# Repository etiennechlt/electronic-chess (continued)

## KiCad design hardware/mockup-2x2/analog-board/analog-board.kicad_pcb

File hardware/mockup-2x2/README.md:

# Maquette 2 x 2 : commande, montage, mise en route

> Remplacée par l'ADR 0010 : la maquette n'est plus construite, le
> plateau 8 x 8 est conçu directement en quadrants. Ce dossier reste
> la référence de la chaîne analogique et du routage. Depuis le
> 07/10/2026 sa carte bobines, rendue passive, est la carte du
> **pilote simple** et la carte analogique son shield possible :
> voir la [fiche du pilote](../../docs/bom-pilote.md).

Deux cartes (ADR 0008) : la carte bobines (100 x 100, 4 couches,
passive) et la carte analogique (100 x 62, 2 couches, assemblée). Le
MCU est une Nucleo-G474RE du commerce reliée en nappes Dupont.

## 0. Ouvrir les cartes dans KiCad

Chaque carte a son fichier projet `.kicad_pro` à côté du `.kicad_pcb`,
généré en même temps que lui : c'est ce fichier qu'on ouvre, KiCad ne
sachant pas ouvrir une carte seule depuis son gestionnaire de projet.

```bash
kicad hardware/mockup-2x2/analog-board/analog-board.kicad_pro
kicad hardware/mockup-2x2/coil-board/coil-board.kicad_pro
```

Sous macOS ou Windows, double clic sur le `.kicad_pro` (ou KiCad,
Fichier, Ouvrir un projet). La carte s'ouvre avec les règles du
générateur déjà en place : classe de nets, largeurs de piste et vias
proposés au routage, minima du DRC. Le projet de la carte analogique
associe aussi son schéma, ouvrable depuis le même gestionnaire.

Trois choses à savoir :

- Les fichiers sont au format KiCad 7. KiCad 8 ou 9 les ouvre et
  propose la conversion au premier enregistrement.
- Symboles et empreintes sont embarqués dans les fichiers : aucune
  bibliothèque à installer, aucune table de bibliothèques à régler.
- KiCad réécrit le `.kicad_pro` en enregistrant (état des fenêtres) et
  crée un `.kicad_prl` local, ignoré par git. Une régénération remet
  le projet dans son état canonique.

Sans KiCad : les rendus `docs/images/analog-board.png` et
`docs/images/coil-board.png`, ou les zip de gerbers dans une
visionneuse.

## 1. Commander

### Carte bobines (8 à 15 EUR les 5, plus l'option cuivre interne)

`sh hardware/mockup-2x2/coil-board/export.sh` regénère la carte et
produit `coil-board-gerbers.zip` (commité avec son empreinte). JLCPCB :
4 couches, 1,6 mm, 1 oz externe, cuivre interne 1 oz en option (note 23,
paragraphe 3.1), pas d'assemblage : la carte est passive, les LED sont
coupées par `leds.fitted` dans le yaml.

### Carte analogique (~60 EUR les 5 dont 2 assemblées)

`analog-board/` contient le projet KiCad, `jlc-bom.csv` et
`jlc-cpl.csv`. JLCPCB : 2 couches, 1,6 mm, assemblage face top.
Important : les codes LCSC du BOM sont des candidats plausibles saisis
hors ligne ; l'outil de commande JLC rapproche aussi par référence
fabricant (MPN) et signale tout écart : vérifier chaque ligne dans
leur prévisualisation avant de payer, en particulier TPS62150RGTR,
AD8421ARZ, OPA2810IDR, 74HCT4052PW, ADuM1201ARZ. Les composants
introuvables en assemblage (souvent l'AD8421) se commandent chez
Mouser ou DigiKey et se soudent à la main (SOIC, facile).

### Le reste (~70 EUR)

Voir `docs/bom-maquette.md` : Nucleo-G474RE, condensateurs C0G des
résonateurs, fil émaillé, aimants ferrite et N42, contreplaqué sec 3 à 6 mm,
feutre, visserie, impression des pièces de `mechanical/`.

## 2. Assembler

1. Carte analogique : souder les traversants (jack, barrettes J2 J4
   J5, JP1 JP3) ; laisser R66 et R67 non montées (elles court-circuitent
   l'isolateur UART).
2. Carte bobines : souder la barrette coudée 1 x 12 mâle pointant vers
   le nord ; entretoises M3 x 25 aux quatre coins.
3. Emboîter la barrette dans le connecteur femelle coudé J2 de la
   carte analogique : les deux cartes sont coplanaires, broche 1 sur
   broche 1 (x = 38,57 mm sur les deux).
4. Support d'aimant : visser la platine sous S3, monter la coupelle
   sur sa vis M3.
5. Bobiner les 4 résonateurs (gabarits imprimés, fil 0,25 mm, tours
   par classe donnés par `python -m chessboard_calc report`), souder
   chaque condensateur C0G, coller bobine et aimant dans les pucks,
   feutre dessous.
6. Percer la planche de contreplaqué avec le gabarit `surface-template`
   (trous de visserie et points lumineux des LED), puis la poser sur les
   entretoises au dessus de
   la carte bobines.

## 3. Câbler la Nucleo

Nappes Dupont femelle-femelle de J4 vers la Nucleo (UM2505), table
générée depuis `config/board.yaml` (section `nucleo_pins`) :

| J4 | Signal | Nucleo |
|---|---|---|
| 1 | 3V3 | 3V3 |
| 2, 4, 19 | GND | GND |
| 3 | AMP_OUT | A0 (PA0), en pont vers A1 (PA1) pour la voie B |
| 5 | MUX_A0 | D3 (PB3) |
| 6 | MUX_A1 | D4 (PB5) |
| 7 | MUX_INH | D5 (PB4) |
| 8 | PULSE_EN | A2 (PA4) |
| 9 a 12 | DRIVE1..4 | D11 (PA7), D12 (PA6), D14 (PB9), D15 (PB8) |
| 13 a 16 | DAMP1..4_N | D6 (PB10), D7 (PA8), D9 (PC7), D10 (PB6) |
| 17 | MCU_TX | D8 (PA9) |
| 18 | MCU_RX | D2 (PA10) |
| 20 | INA_OUT | libre (oscilloscope) |

## 4. Mise en route

1. Flasher `firmware/mockup` (`make`, copier le .bin sur le lecteur
   NUCLEO). Console VCP 921600 bauds.
2. Alimenter le 12 V (JP1 côté LDO pour commencer, JP3 côté FPWM).
3. `h` puis `s` : quatre lignes CSV. Sans puck, amp_mv doit rester
   faible ; poser un puck doit faire apparaître sa fréquence.
4. Vérifier la voie B au générateur de fonctions sur AMP_OUT (voir
   `firmware/mockup/README.md`, points à vérifier).
5. Dérouler `measurements/protocol.md`.

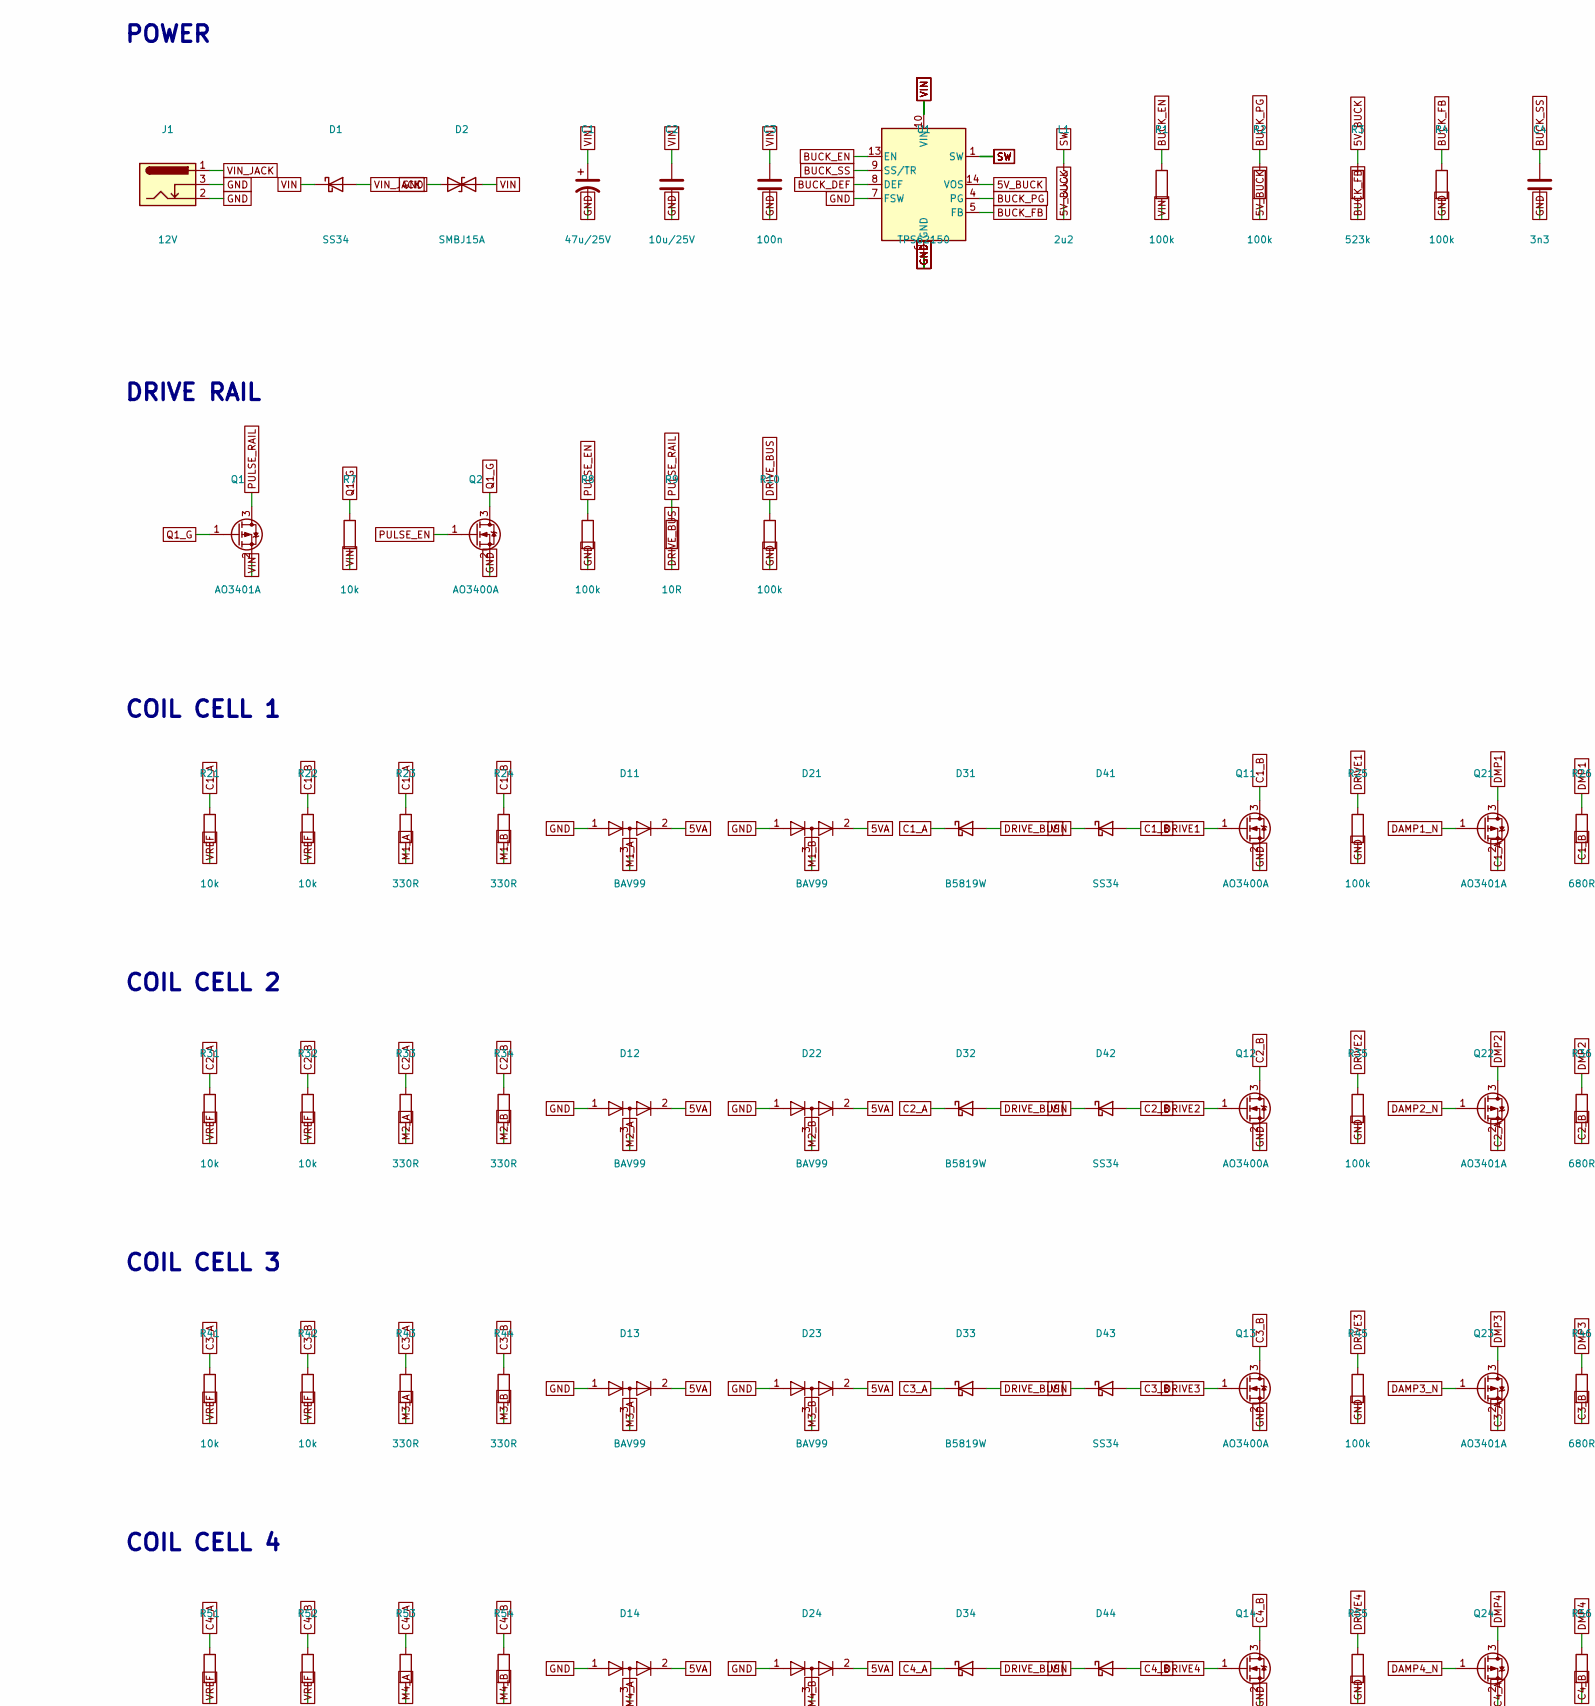
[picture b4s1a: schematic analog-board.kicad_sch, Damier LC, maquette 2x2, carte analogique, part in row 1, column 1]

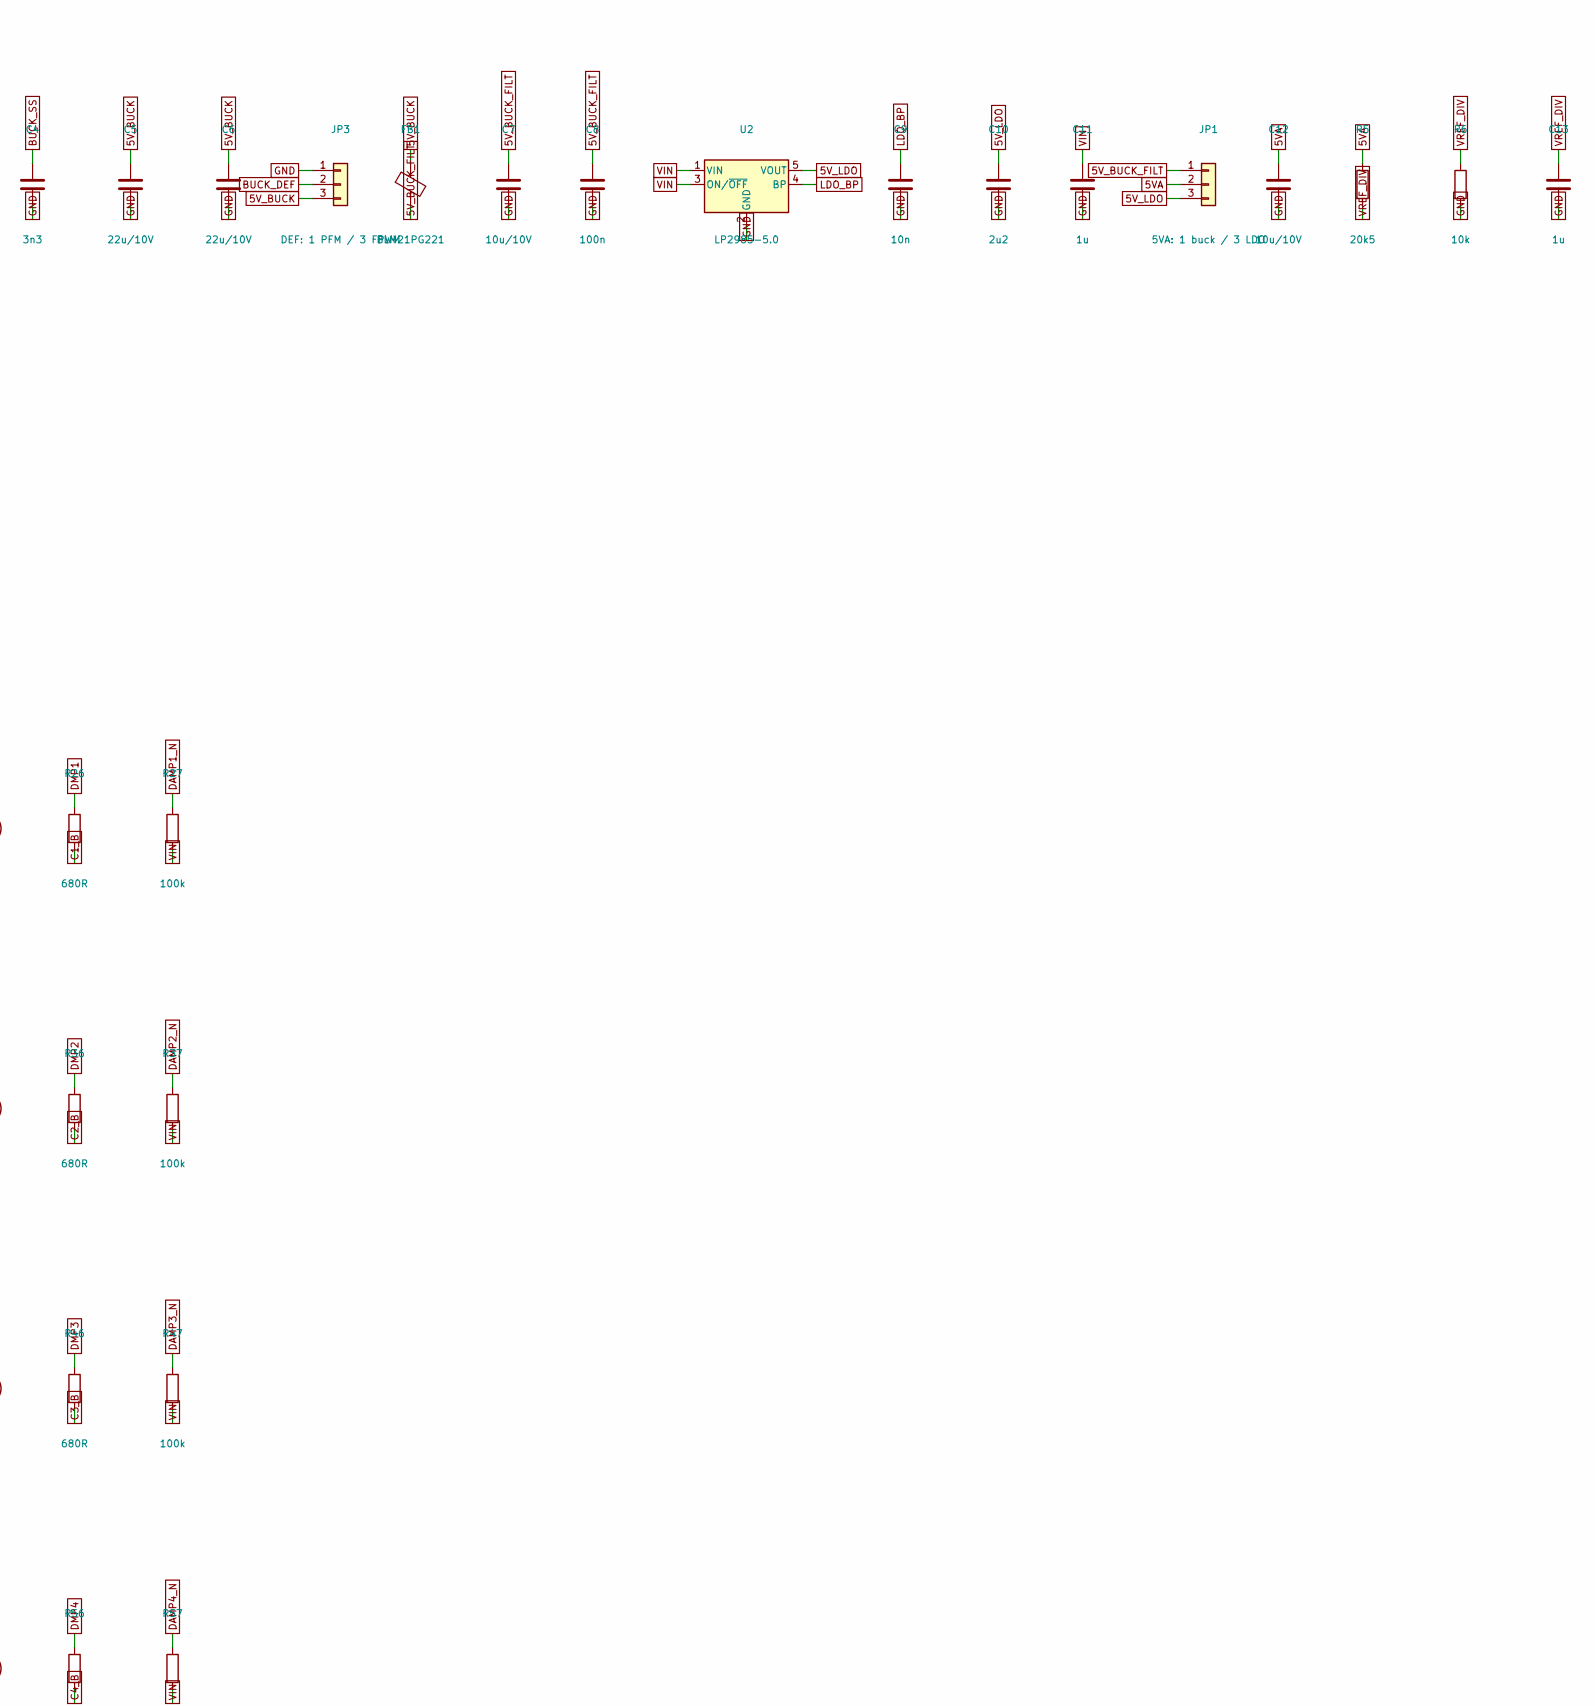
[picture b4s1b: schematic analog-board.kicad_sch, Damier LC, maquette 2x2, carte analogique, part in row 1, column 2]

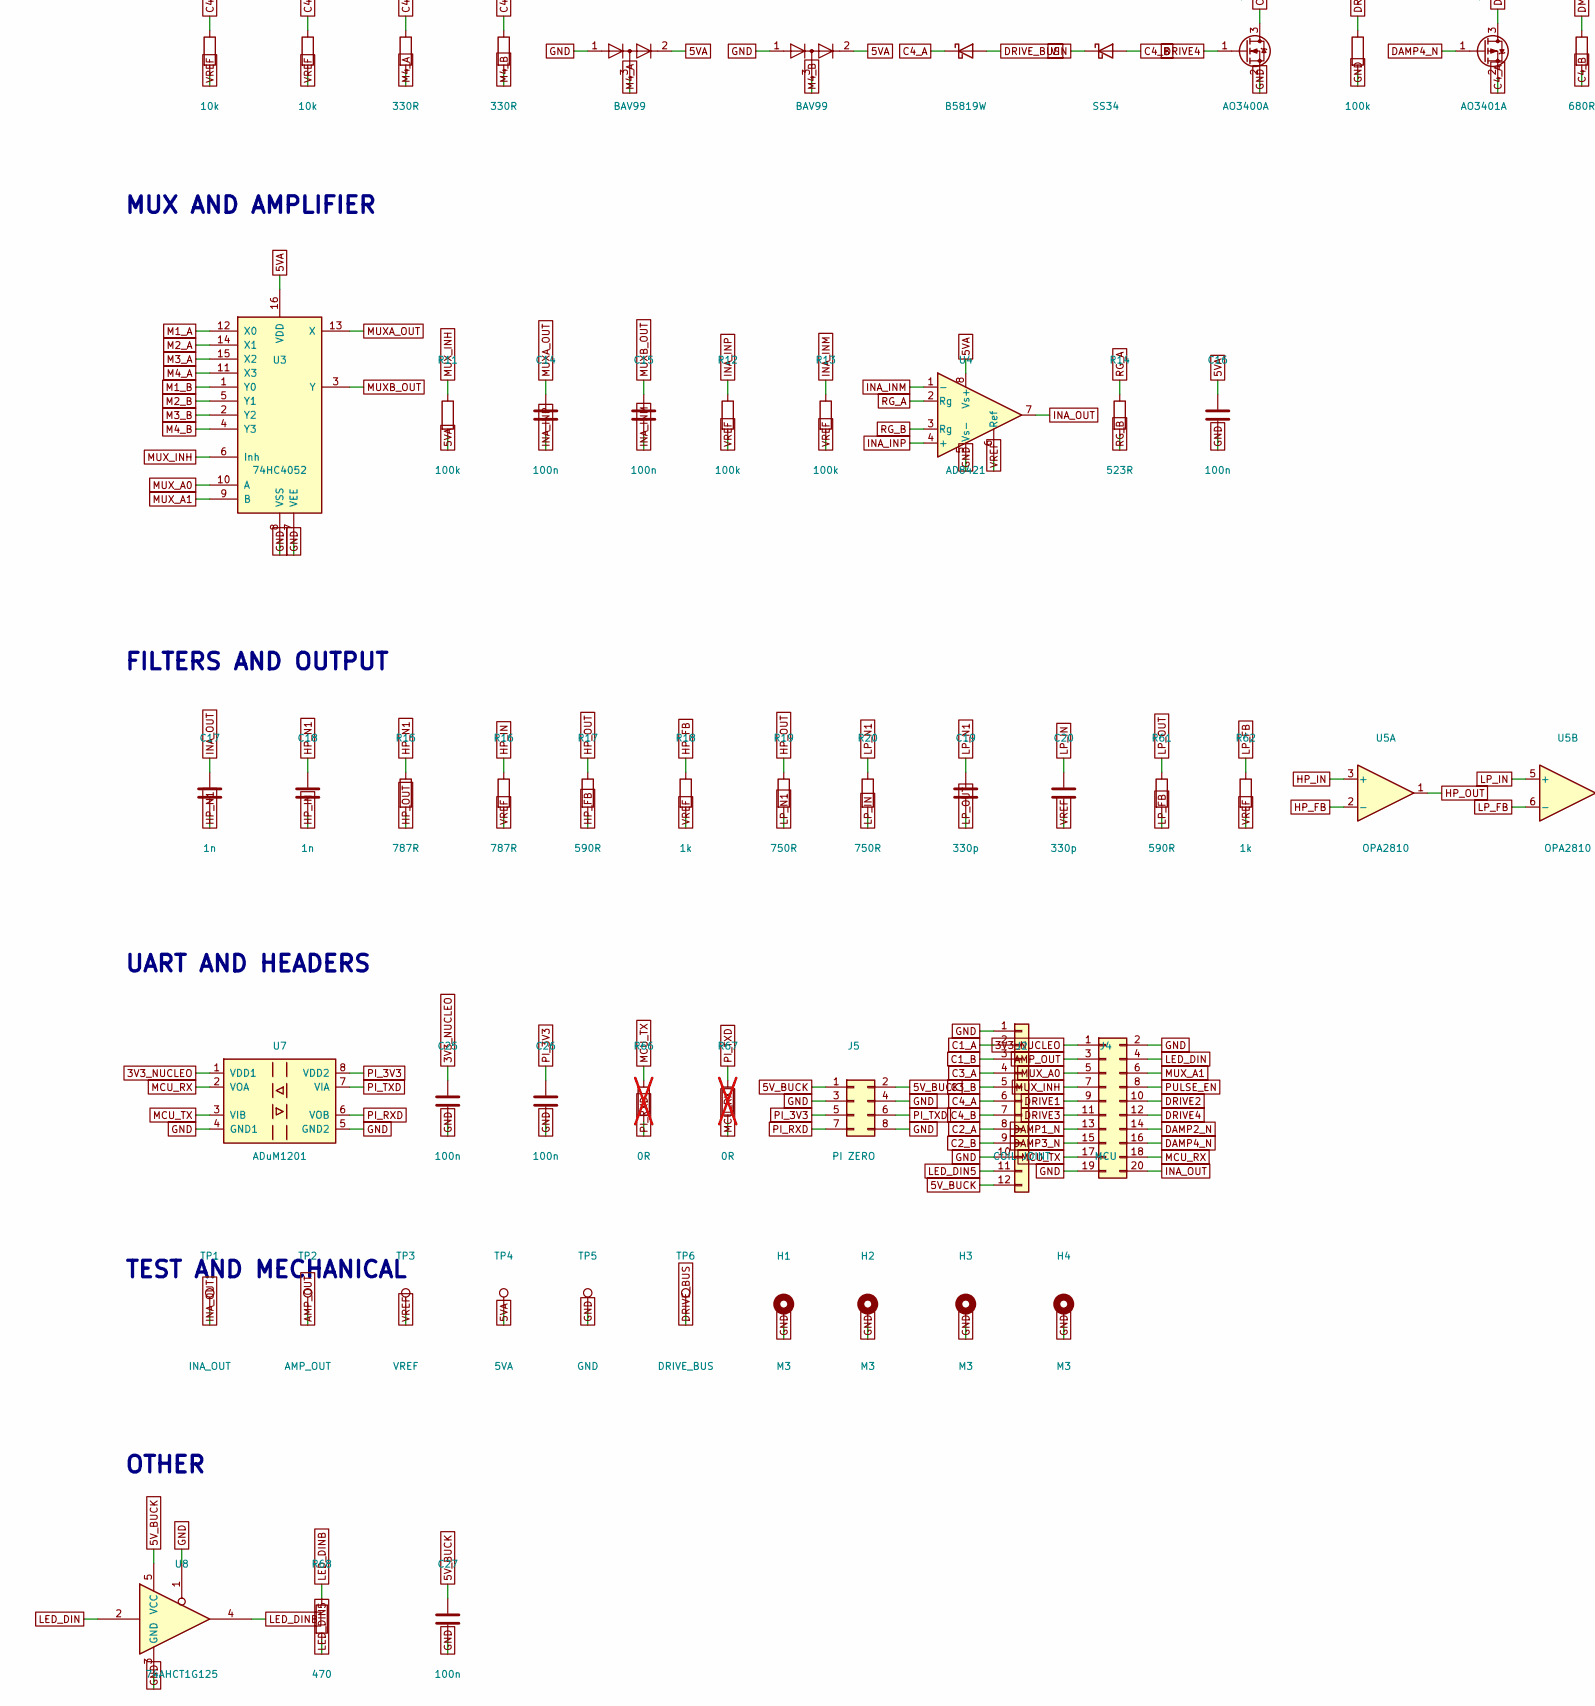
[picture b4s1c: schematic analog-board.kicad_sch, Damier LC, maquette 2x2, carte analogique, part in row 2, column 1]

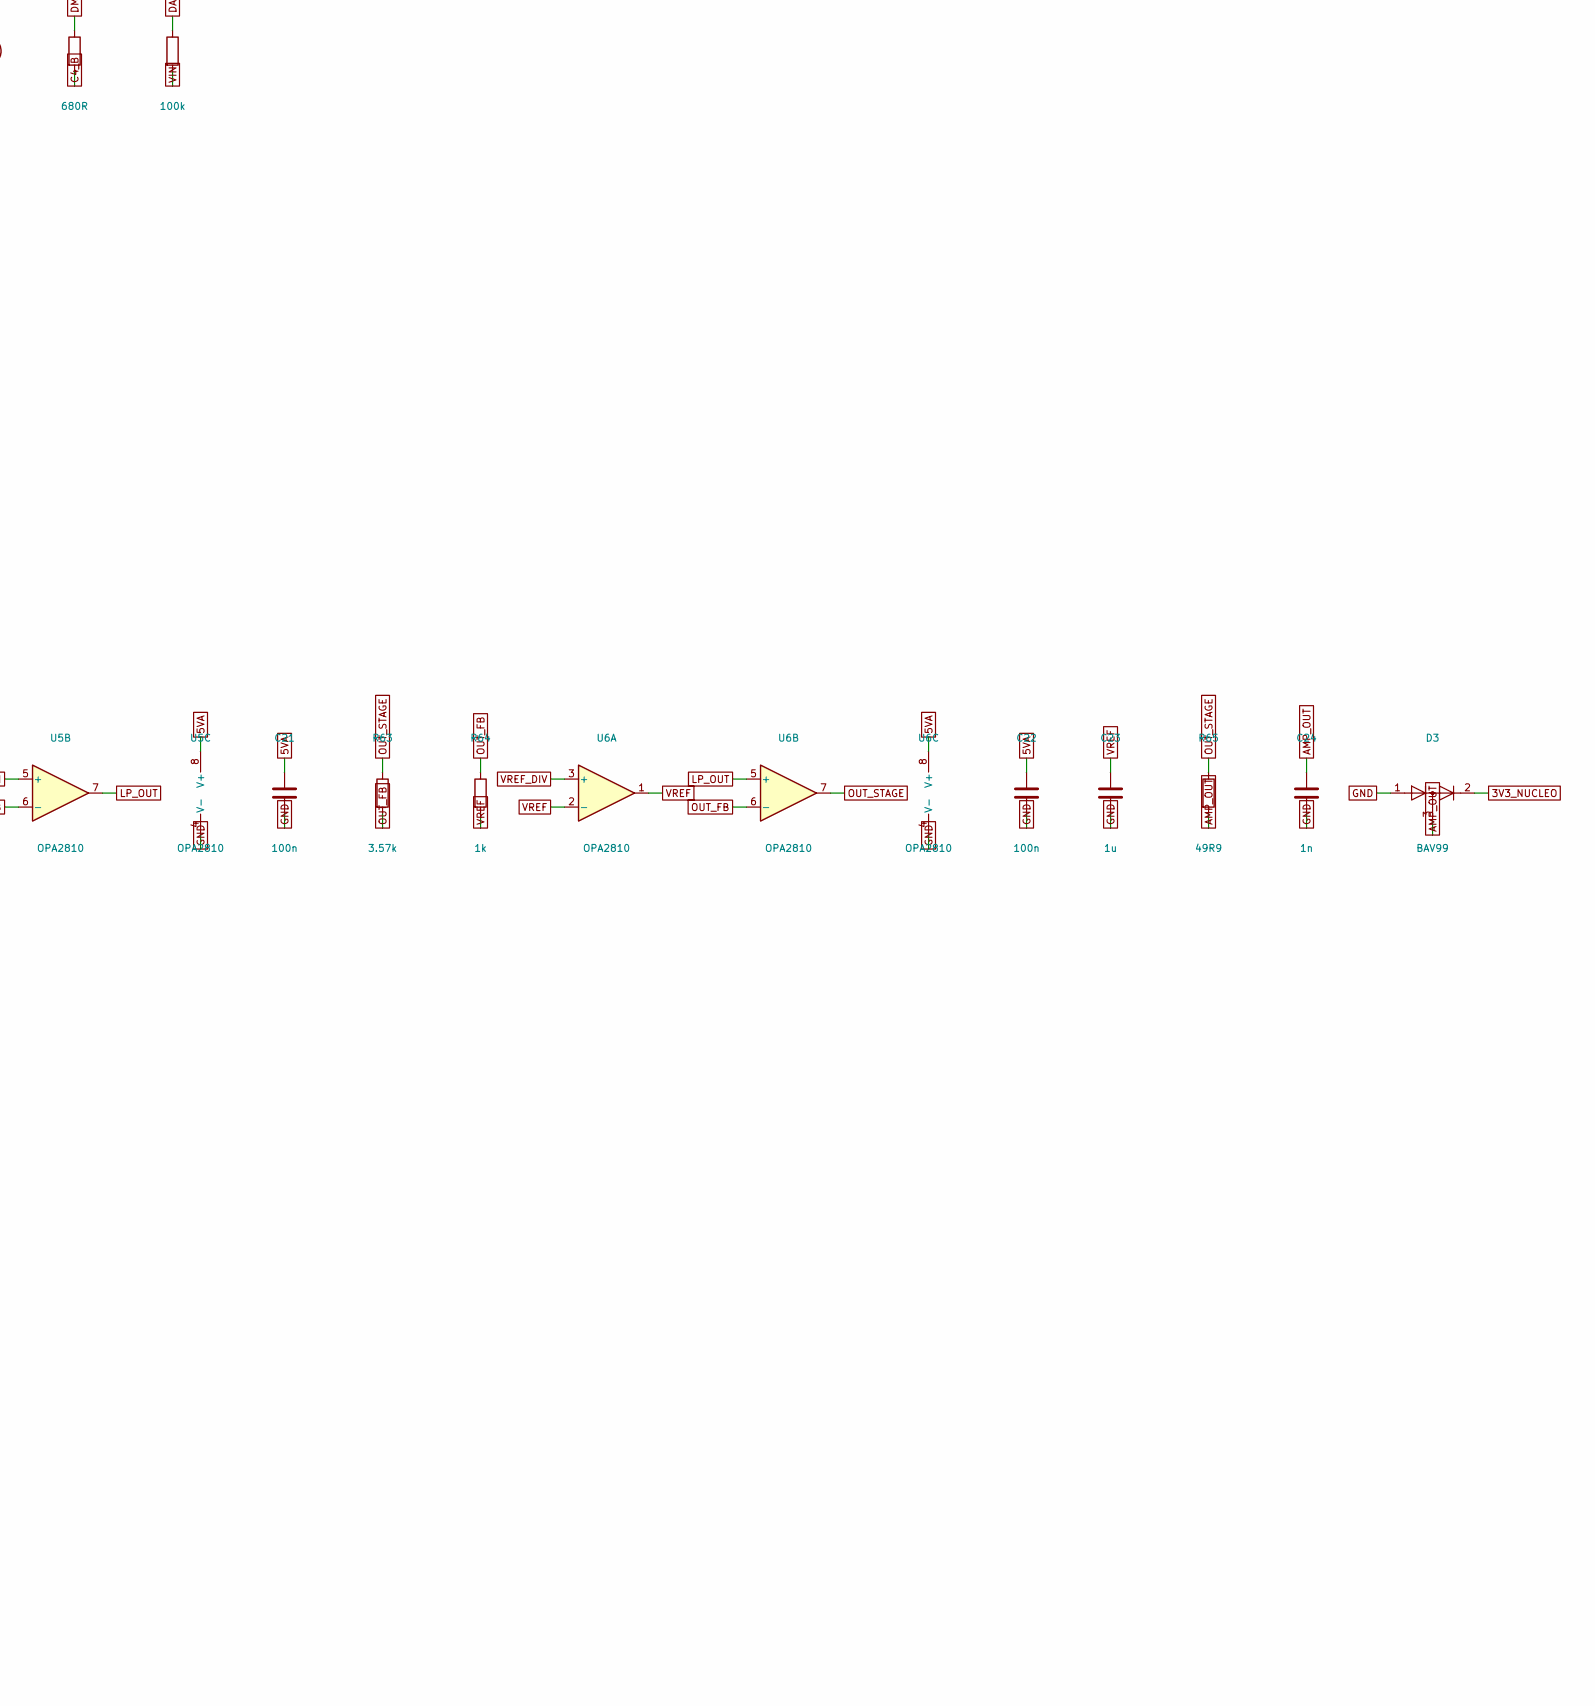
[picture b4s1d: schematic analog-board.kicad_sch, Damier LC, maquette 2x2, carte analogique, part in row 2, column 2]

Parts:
C1: 47u/25V; CP_Elec_6.3x7.7
C2: 10u/25V; C_1206_3216Metric
C3, C8, C14, C15, C16, C21, C22, C25, C26, C27: 100n; C_0603_1608Metric
C4: 3n3; C_0603_1608Metric
C5, C6: 22u/10V; C_1206_3216Metric
C7, C12: 10u/10V; C_1206_3216Metric
C9: 10n; C_0603_1608Metric
C10: 2u2; C_0603_1608Metric
C11, C13, C23: 1u; C_0603_1608Metric
C17, C18, C24: 1n; C_0603_1608Metric
C19, C20: 330p; C_0603_1608Metric
D1, D41, D42, D43, D44: SS34; D_SMA; MPN SS34; LCSC C8678
D2: SMBJ15A; D_SMB; MPN SMBJ15A; LCSC C113962
D3, D11, D12, D13, D14, D21, D22, D23, D24: BAV99; SOT-23; MPN BAV99; LCSC C2500
D31, D32, D33, D34: B5819W; D_SOD-123; MPN B5819W; LCSC C8598
FB1: BLM21PG221; R_0805_2012Metric; MPN BLM21PG221SN1D; LCSC C18305
H1, H2, H3, H4: M3; MountingHole_3.2mm_M3_Pad
J1: 12V; BarrelJack_Horizontal; MPN DC-005-5.5x2.1; LCSC C381118
J2: COIL JOINT; PinHeader_1x12_P2.54mm_Vertical
J4: MCU; PinHeader_2x10_P2.54mm_Vertical
J5: PI ZERO; PinHeader_2x04_P2.54mm_Vertical
JP1: 5VA: 1 buck / 3 LDO; PinHeader_1x03_P2.54mm_Vertical
JP3: DEF: 1 PFM / 3 FPWM; PinHeader_1x03_P2.54mm_Vertical
L1: 2u2; L_Bourns-SRN4018; MPN SRN4018TA2R2M; LCSC C2827538
Q1, Q21, Q22, Q23, Q24: AO3401A; SOT-23; MPN AO3401A; LCSC C15127
Q2, Q11, Q12, Q13, Q14: AO3400A; SOT-23; MPN AO3400A; LCSC C20917
R1, R2, R4, R8, R10, R11, R12, R13, R25, R27, R35, R37, R45, R47, R55, R57: 100k; R_0603_1608Metric
R3: 523k; R_0603_1608Metric
R5: 20k5; R_0603_1608Metric
R6, R7, R21, R22, R31, R32, R41, R42, R51, R52: 10k; R_0603_1608Metric
R9: 10R; R_2512_6332Metric
R14: 523R; R_0603_1608Metric
R15, R16: 787R; R_0603_1608Metric
R17, R61: 590R; R_0603_1608Metric
R18, R62, R64: 1k; R_0603_1608Metric
R19, R20: 750R; R_0603_1608Metric
R23, R24, R33, R34, R43, R44, R53, R54: 330R; R_0603_1608Metric
R26, R36, R46, R56: 680R; R_0805_2012Metric
R63: 3.57k; R_0603_1608Metric
R65: 49R9; R_0603_1608Metric
R66, R67: 0R; R_0603_1608Metric; not fitted
R68: 470; R_0603_1608Metric
TP1: INA_OUT; TestPoint_Pad_1.5x1.5mm
TP2: AMP_OUT; TestPoint_Pad_1.5x1.5mm
TP3: VREF; TestPoint_Pad_1.5x1.5mm
TP4: 5VA; TestPoint_Pad_1.5x1.5mm
TP5: GND; TestPoint_Pad_1.5x1.5mm
TP6: DRIVE_BUS; TestPoint_Pad_1.5x1.5mm
U1: TPS62150; QFN-16-1EP_3x3mm_P0.5mm_EP1.75x1.75mm; MPN TPS62150RGTR; LCSC C72631
U2: LP2985-5.0; SOT-23-5; MPN LP2985AIM5-5.0; LCSC C129541
U3: 74HC4052; TSSOP-16_4.4x5mm_P0.65mm; MPN 74HCT4052PW; LCSC C57078
U4: AD8421; SOIC-8_3.9x4.9mm_P1.27mm; MPN AD8421ARZ; LCSC C462186
U5, U6: OPA2810; SOIC-8_3.9x4.9mm_P1.27mm; MPN OPA2810IDR; LCSC C2059830
U7: ADuM1201; SOIC-8_3.9x4.9mm_P1.27mm; MPN ADuM1201ARZ; LCSC C123211
U8: 74AHCT1G125; SOT-23-5; MPN SN74AHCT1G125DBVR; LCSC C350557

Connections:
3V3_NUCLEO: C25.1, D3.2 (A), J4.1, U7.1 (VDD1)
5VA: C12.1, C16.1, C21.1, C22.1, D11.2 (A), D12.2 (A), D13.2 (A), D14.2 (A), D21.2 (A), D22.2 (A), D23.2 (A), D24.2 (A), JP1.2, R5.1, R11.2, TP4.1, U3.16 (VDD), U4.8 (Vs+), U5.8 (V+), U6.8 (V+)
5V_BUCK: C5.1, C6.1, C27.1, FB1.1, J2.12, J5.1, J5.2, JP3.3, L1.2, R2.2, R3.1, U1.14 (VOS), U8.5 (VCC)
5V_BUCK_FILT: C7.1, C8.1, FB1.2, JP1.1
5V_LDO: C10.1, JP1.3, U2.5 (VOUT)
AMP_OUT: C24.1, D3.3 (K), J4.3, R65.2, TP2.1
BUCK_DEF: JP3.2, U1.8 (DEF)
BUCK_EN: R1.1, U1.13 (EN)
BUCK_FB: R3.2, R4.1, U1.5 (FB)
BUCK_PG: R2.1, U1.4 (PG)
BUCK_SS: C4.1, U1.9 (SS/TR)
C1_A: D31.1 (K), J2.2, Q21.2 (S), R21.1, R23.1
C1_B: D41.2 (A), J2.3, Q11.3 (D), R22.1, R24.1, R26.2
C2_A: D32.1 (K), J2.8, Q22.2 (S), R31.1, R33.1
C2_B: D42.2 (A), J2.9, Q12.3 (D), R32.1, R34.1, R36.2
C3_A: D33.1 (K), J2.4, Q23.2 (S), R41.1, R43.1
C3_B: D43.2 (A), J2.5, Q13.3 (D), R42.1, R44.1, R46.2
C4_A: D34.1 (K), J2.6, Q24.2 (S), R51.1, R53.1
C4_B: D44.2 (A), J2.7, Q14.3 (D), R52.1, R54.1, R56.2
DAMP1_N: J4.13, Q21.1 (G), R27.1
DAMP2_N: J4.14, Q22.1 (G), R37.1
DAMP3_N: J4.15, Q23.1 (G), R47.1
DAMP4_N: J4.16, Q24.1 (G), R57.1
DMP1: Q21.3 (D), R26.1
DMP2: Q22.3 (D), R36.1
DMP3: Q23.3 (D), R46.1
DMP4: Q24.3 (D), R56.1
DRIVE1: J4.9, Q11.1 (G), R25.1
DRIVE2: J4.10, Q12.1 (G), R35.1
DRIVE3: J4.11, Q13.1 (G), R45.1
DRIVE4: J4.12, Q14.1 (G), R55.1
DRIVE_BUS: D31.2 (A), D32.2 (A), D33.2 (A), D34.2 (A), R9.2, R10.1, TP6.1
GND: C1.2, C2.2, C3.2, C4.2, C5.2, C6.2, C7.2, C8.2, C9.2, C10.2, C11.2, C12.2, C13.2, C16.2, C21.2, C22.2, C23.2, C24.2, C25.2, C26.2, C27.2, D2.1 (A1), D3.1 (K), D11.1 (K), D12.1 (K), D13.1 (K), D14.1 (K), D21.1 (K), D22.1 (K), D23.1 (K), D24.1 (K), H1.1, H2.1, H3.1, H4.1, J1.2, J1.3, J2.1, J2.10, J4.2, J4.19, J5.3, J5.4, J5.8, JP3.1, Q2.2 (S), Q11.2 (S), Q12.2 (S), Q13.2 (S), Q14.2 (S), R4.2, R6.2, R8.2, R10.2, R25.2, R35.2, R45.2, R55.2, TP5.1, U1.6 (GND), U1.7 (FSW), U1.15 (GND), U1.16 (GND), U1.17 (GND), U2.2 (GND), U3.7 (VEE), U3.8 (VSS), U4.5 (Vs-), U5.4 (V-), U6.4 (V-), U7.4 (GND1), U7.5 (GND2), U8.1, U8.3 (GND)
HP_FB: R17.2, R18.1, U5.2 (-)
HP_IN: C18.2, R16.1, U5.3 (+)
HP_N1: C17.2, C18.1, R15.1
HP_OUT: R15.2, R17.1, R19.1, U5.1
INA_INM: C15.2, R13.1, U4.1 (-)
INA_INP: C14.2, R12.1, U4.4 (+)
INA_OUT: C17.1, J4.20, TP1.1, U4.7
LDO_BP: C9.1, U2.4 (BP)
LED_DIN: J4.4, U8.2
LED_DIN5: J2.11, R68.2
LED_DINB: R68.1, U8.4
LP_FB: R61.2, R62.1, U5.6 (-)
LP_IN: C20.1, R20.2, U5.5 (+)
LP_N1: C19.1, R19.2, R20.1
LP_OUT: C19.2, R61.1, U5.7, U6.5 (+)
M1_A: D11.3 (K), R23.2, U3.12 (X0)
M1_B: D21.3 (K), R24.2, U3.1 (Y0)
M2_A: D12.3 (K), R33.2, U3.14 (X1)
M2_B: D22.3 (K), R34.2, U3.5 (Y1)
M3_A: D13.3 (K), R43.2, U3.15 (X2)
M3_B: D23.3 (K), R44.2, U3.2 (Y2)
M4_A: D14.3 (K), R53.2, U3.11 (X3)
M4_B: D24.3 (K), R54.2, U3.4 (Y3)
MCU_RX: J4.18, R67.2, U7.2 (VOA)
MCU_TX: J4.17, R66.1, U7.3 (VIB)
MUXA_OUT: C14.1, U3.13 (X)
MUXB_OUT: C15.1, U3.3 (Y)
MUX_A0: J4.5, U3.10 (A)
MUX_A1: J4.6, U3.9 (B)
MUX_INH: J4.7, R11.1, U3.6 (Inh)
OUT_FB: R63.2, R64.1, U6.6 (-)
OUT_STAGE: R63.1, R65.1, U6.7
PI_3V3: C26.1, J5.5, U7.8 (VDD2)
PI_RXD: J5.7, R66.2, U7.6 (VOB)
PI_TXD: J5.6, R67.1, U7.7 (VIA)
PULSE_EN: J4.8, Q2.1 (G), R8.1
PULSE_RAIL: Q1.3 (D), R9.1
Q1_G: Q1.1 (G), Q2.3 (D), R7.1
RG_A: R14.1, U4.2 (Rg)
RG_B: R14.2, U4.3 (Rg)
SW: L1.1, U1.1 (SW), U1.2 (SW), U1.3 (SW)
VIN: C1.1, C2.1, C3.1, C11.1, D1.1 (K), D2.2 (A2), D41.1 (K), D42.1 (K), D43.1 (K), D44.1 (K), Q1.2 (S), R1.2, R7.2, R27.2, R37.2, R47.2, R57.2, U1.10 (VIN), U1.11 (VIN), U1.12 (VIN), U2.1 (VIN), U2.3 (ON/~OFF)
VIN_JACK: D1.2 (A), J1.1
VREF: C20.2, C23.1, R12.2, R13.2, R16.2, R18.2, R21.2, R22.2, R31.2, R32.2, R41.2, R42.2, R51.2, R52.2, R62.2, R64.2, TP3.1, U4.6 (Ref), U6.1, U6.2 (-)
VREF_DIV: C13.1, R5.2, R6.1, U6.3 (+)

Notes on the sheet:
POWER
DRIVE RAIL
COIL CELL 1
COIL CELL 2
COIL CELL 3
COIL CELL 4
MUX AND AMPLIFIER
FILTERS AND OUTPUT
UART AND HEADERS
TEST AND MECHANICAL
OTHER

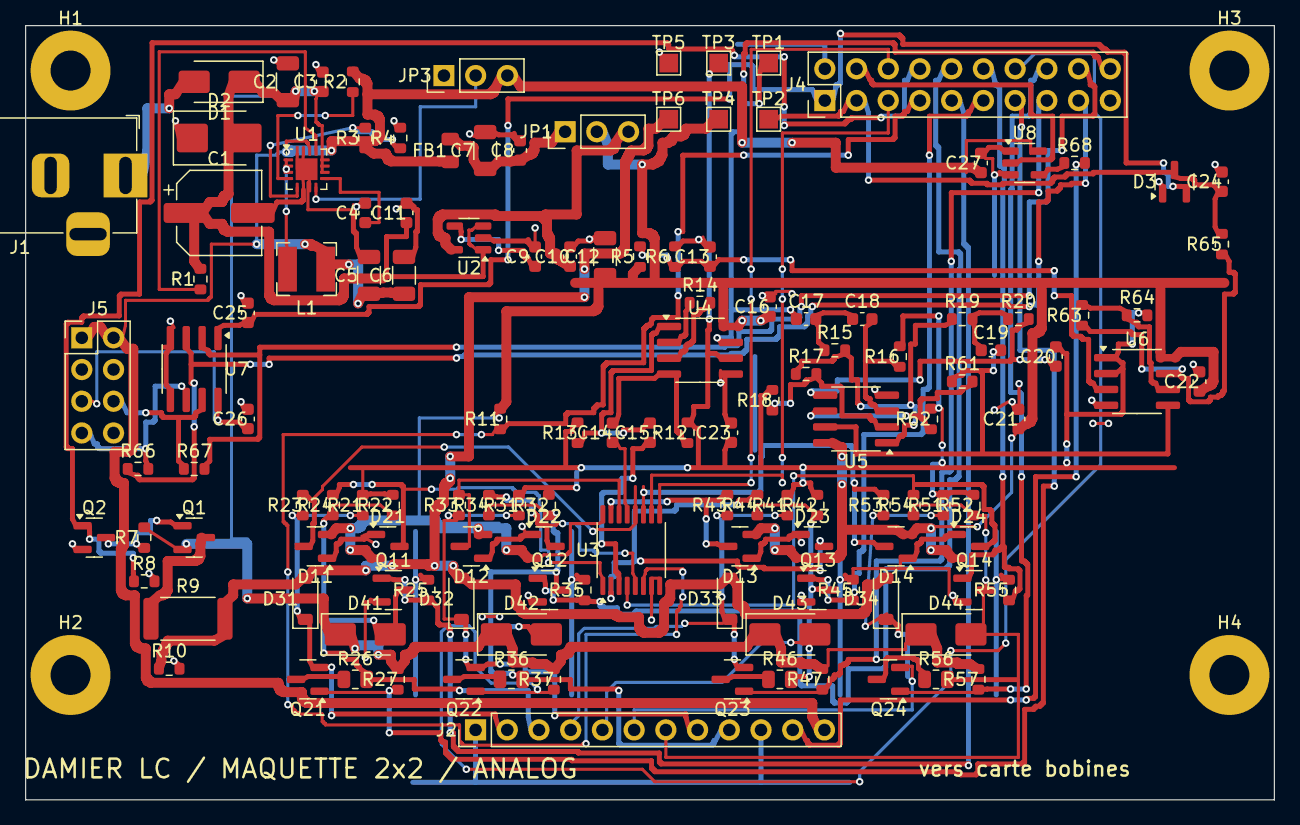
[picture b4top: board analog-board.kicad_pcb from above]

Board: 2 copper layers, 100.0 x 62.0 mm, 138 parts (0 on the bottom side), 78 nets.

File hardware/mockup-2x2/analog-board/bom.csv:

References,Qty,Value,Footprint,MPN,LCSC,DNP
C1,1,47u/25V,CP_Elec_6.3x7.7,,,
C10,1,2u2,C_0603_1608Metric,,,
C11 C13 C23,3,1u,C_0603_1608Metric,,,
C17 C18 C24,3,1n,C_0603_1608Metric,,,
C19 C20,2,330p,C_0603_1608Metric,,,
C2,1,10u/25V,C_1206_3216Metric,,,
C14 C15 C16 C21 C22 C25 C26 C27 C3 C8,10,100n,C_0603_1608Metric,,,
C4,1,3n3,C_0603_1608Metric,,,
C5 C6,2,22u/10V,C_1206_3216Metric,,,
C12 C7,2,10u/10V,C_1206_3216Metric,,,
C9,1,10n,C_0603_1608Metric,,,
D1 D41 D42 D43 D44,5,SS34,D_SMA,SS34,C8678,
D11 D12 D13 D14 D21 D22 D23 D24 D3,9,BAV99,SOT-23,BAV99,C2500,
D2,1,SMBJ15A,D_SMB,SMBJ15A,C113962,
D31 D32 D33 D34,4,B5819W,D_SOD-123,B5819W,C8598,
FB1,1,BLM21PG221,R_0805_2012Metric,BLM21PG221SN1D,C18305,
H1 H2 H3 H4,4,M3,MountingHole_3.2mm_M3_Pad,,,
J1,1,12V,BarrelJack_Horizontal,DC-005-5.5x2.1,C381118,
J2,1,COIL JOINT,PinHeader_1x12_P2.54mm_Vertical,,,
J4,1,MCU,PinHeader_2x10_P2.54mm_Vertical,,,
J5,1,PI ZERO,PinHeader_2x04_P2.54mm_Vertical,,,
JP1,1,5VA: 1 buck / 3 LDO,PinHeader_1x03_P2.54mm_Vertical,,,
JP3,1,DEF: 1 PFM / 3 FPWM,PinHeader_1x03_P2.54mm_Vertical,,,
L1,1,2u2,L_Bourns-SRN4018,SRN4018TA2R2M,C2827538,
Q1 Q21 Q22 Q23 Q24,5,AO3401A,SOT-23,AO3401A,C15127,
Q11 Q12 Q13 Q14 Q2,5,AO3400A,SOT-23,AO3400A,C20917,
R1 R10 R11 R12 R13 R2 R25 R27 R35 R37 R4 R45 R47 R55 R57 R8,16,100k,R_0603_1608Metric,,,
R14,1,523R,R_0603_1608Metric,,,
R15 R16,2,787R,R_0603_1608Metric,,,
R17 R61,2,590R,R_0603_1608Metric,,,
R18 R62 R64,3,1k,R_0603_1608Metric,,,
R19 R20,2,750R,R_0603_1608Metric,,,
R23 R24 R33 R34 R43 R44 R53 R54,8,330R,R_0603_1608Metric,,,
R26 R36 R46 R56,4,680R,R_0805_2012Metric,,,
R3,1,523k,R_0603_1608Metric,,,
R5,1,20k5,R_0603_1608Metric,,,
R21 R22 R31 R32 R41 R42 R51 R52 R6 R7,10,10k,R_0603_1608Metric,,,
R63,1,3.57k,R_0603_1608Metric,,,
R65,1,49R9,R_0603_1608Metric,,,
R66 R67,2,0R,R_0603_1608Metric,,,DNP
R68,1,470,R_0603_1608Metric,,,
R9,1,10R,R_2512_6332Metric,,,
TP1,1,INA_OUT,TestPoint_Pad_1.5x1.5mm,,,
TP2,1,AMP_OUT,TestPoint_Pad_1.5x1.5mm,,,
TP3,1,VREF,TestPoint_Pad_1.5x1.5mm,,,
TP4,1,5VA,TestPoint_Pad_1.5x1.5mm,,,
TP5,1,GND,TestPoint_Pad_1.5x1.5mm,,,
TP6,1,DRIVE_BUS,TestPoint_Pad_1.5x1.5mm,,,
U1,1,TPS62150,QFN-16-1EP_3x3mm_P0.5mm_EP1.75x1.75mm,TPS62150RGTR,C72631,
U2,1,LP2985-5.0,SOT-23-5,LP2985AIM5-5.0,C129541,
U3,1,74HC4052,TSSOP-16_4.4x5mm_P0.65mm,74HCT4052PW,C57078,
U4,1,AD8421,SOIC-8_3.9x4.9mm_P1.27mm,AD8421ARZ,C462186,
U5 U6,2,OPA2810,SOIC-8_3.9x4.9mm_P1.27mm,OPA2810IDR,C2059830,
U7,1,ADuM1201,SOIC-8_3.9x4.9mm_P1.27mm,ADuM1201ARZ,C123211,
U8,1,74AHCT1G125,SOT-23-5,SN74AHCT1G125DBVR,C350557,
